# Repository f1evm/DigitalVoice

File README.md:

# DigitalVoice
An open source codec2 based handheld digital radio for VHF/UHF amateur bands

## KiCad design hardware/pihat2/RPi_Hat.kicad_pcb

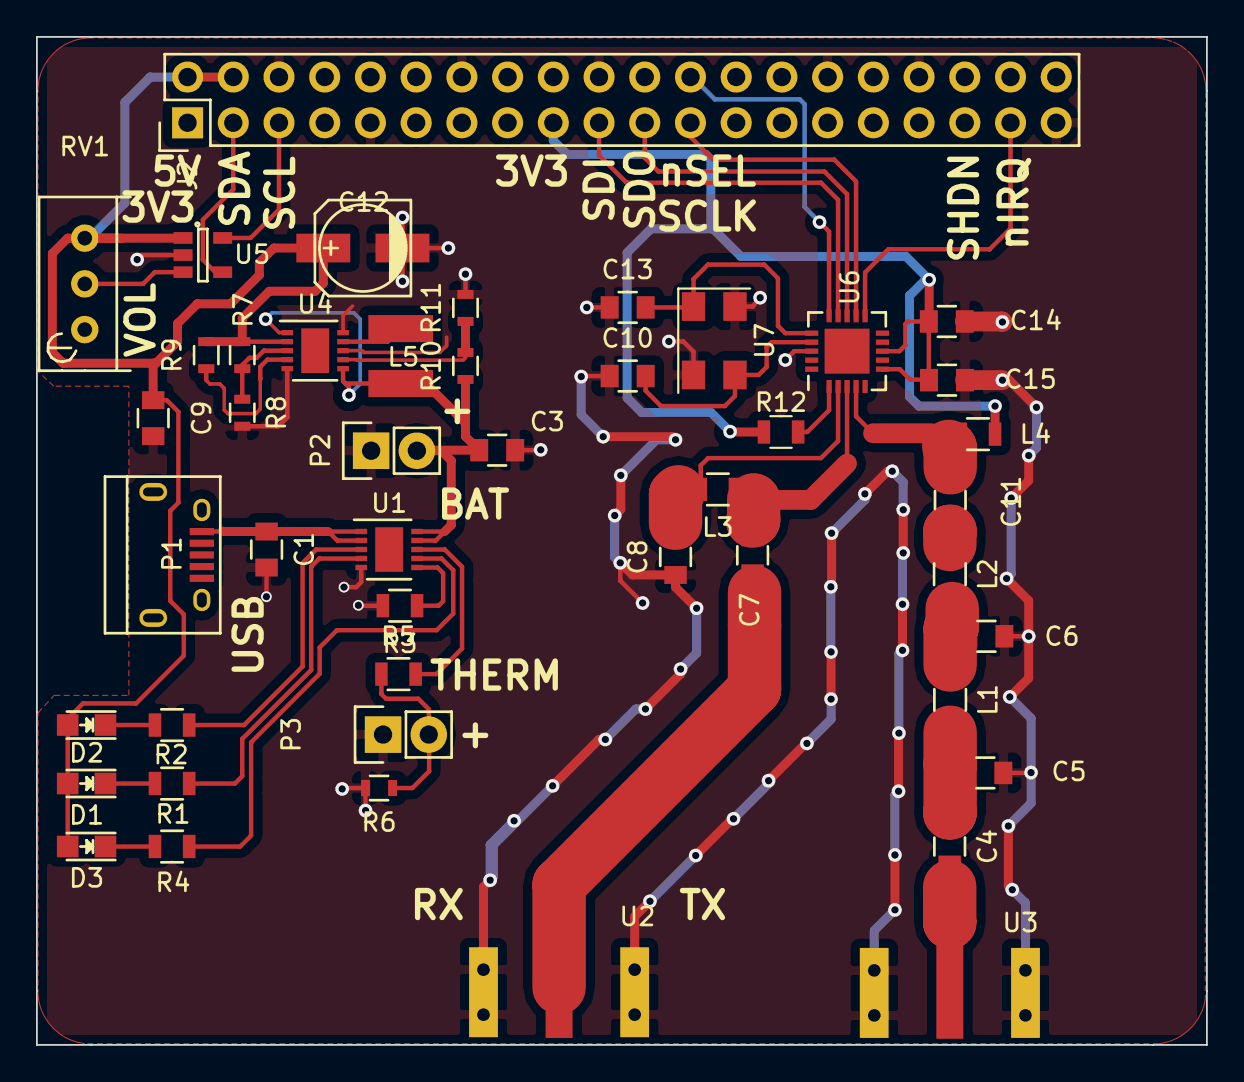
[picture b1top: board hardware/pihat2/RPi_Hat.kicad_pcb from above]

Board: 2 copper layers, 65.0 x 56.0 mm, 46 parts (0 on the bottom side), 34 nets.

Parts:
C1, C3, C9: 10uF; C_0805
C4, C5, C6, C7, C8, C11: C; C_0805
C10, C13: 12pF; C_0805
C12: 47uF; c_elec_5x5.3
C14, C15: 10nF; C_0805
D1, D2, D3: LED; LED_0805
J2: RPi_GPIO; Pin_Header_Straight_2x20
L1, L2, L3, L4: L_Small; R_0805
L5: 6.8uH; BOURNES_SRN4018
P1: USB_OTG; USB_Micro-B
P2: BATT; Pin_Header_Straight_1x02
P3: THERM; Pin_Header_Straight_1x02
R1, R2, R3, R4, R5, R12: 1K; R_0805
R6: 150K; R_0603
R7, R8, R9, R10, R11: R; R_0603
RV1: POT; Potentiometer_Bourns_3296W_3-8Zoll_Inline_ScrewUp
U1: MCP73833; DFN-10-1EP_3x3mm_Pitch0.5mm
U2, U3: SMA_Edge_Mount
U4: TPS61027; DFN-10-1EP_3x3mm_Pitch0.5mm
U5: MCP3021; SOT-23-5
U6: Si4464; QFN-20-1EP_4x4mm_Pitch0.5mm
U7: 30MHz; Crystal_SMD_Abracon_ABM3C-4pin_5.0x3.2mm

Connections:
5VU: C9.1, C12.1, J2.2, J2.4, R7.1, R9.2, RV1.2, U4.2, U5.1
+3V3: C14.2, C15.2, J2.1, J2.17, L4.1, R12.1, U6.6, U6.8
GND: C1.2, C3.2, C5.2, C6.2, C8.1, C9.2, C10.1, C12.2, C13.1, C14.1, C15.1, J2.6, J2.9, J2.14, J2.20, J2.25, J2.30, J2.34, J2.39, P2.1, P3.1, R3.2, R6.2, R8.2, R11.2, U1.5, U2.1, U2.3, U3.1, U3.3, U4.5, U4.8, U4.10, U5.2, U6.18, U7.2, U7.4
unnamed: C4.1, C5.1, L1.2
unnamed: C6.1, L1.1, L2.2
unnamed: C7.1, L3.1, U6.3
unnamed: C8.2, L3.2, U6.2
unnamed: C10.2, U6.17, U7.3
unnamed: C11.1, L4.2, U6.4
unnamed: C11.2, L2.1
unnamed: C13.2, U6.16, U7.1
unnamed: L5.1, U4.9
unnamed: P3.2, R5.1, R6.1
unnamed: R1.2, U1.4
unnamed: R2.2, U1.3
unnamed: R3.1, U1.6
unnamed: R4.2, U1.7
unnamed: R5.2, U1.8
unnamed: R7.2, R8.1, U4.3
unnamed: R9.1, U4.4
unnamed: R10.2, R11.1, U4.7
unnamed: R12.2, U6.1
RXI: C7.2, U2.2
SCL: J2.5, U5.5
SCLK: J2.23, U6.12
SDA: J2.3, U5.4
SDI: J2.19, U6.14
SDO: J2.21, U6.13
TXO: C4.2, U3.2
USB_5V: C1.1, U1.1, U1.2
VBAT: C3.1, L5.2, P2.2, R10.1, U1.9, U1.10, U4.1, U4.6
VOL: RV1.1, U5.3
nIRQ: J2.37, U6.11
nSEL: J2.24, U6.15

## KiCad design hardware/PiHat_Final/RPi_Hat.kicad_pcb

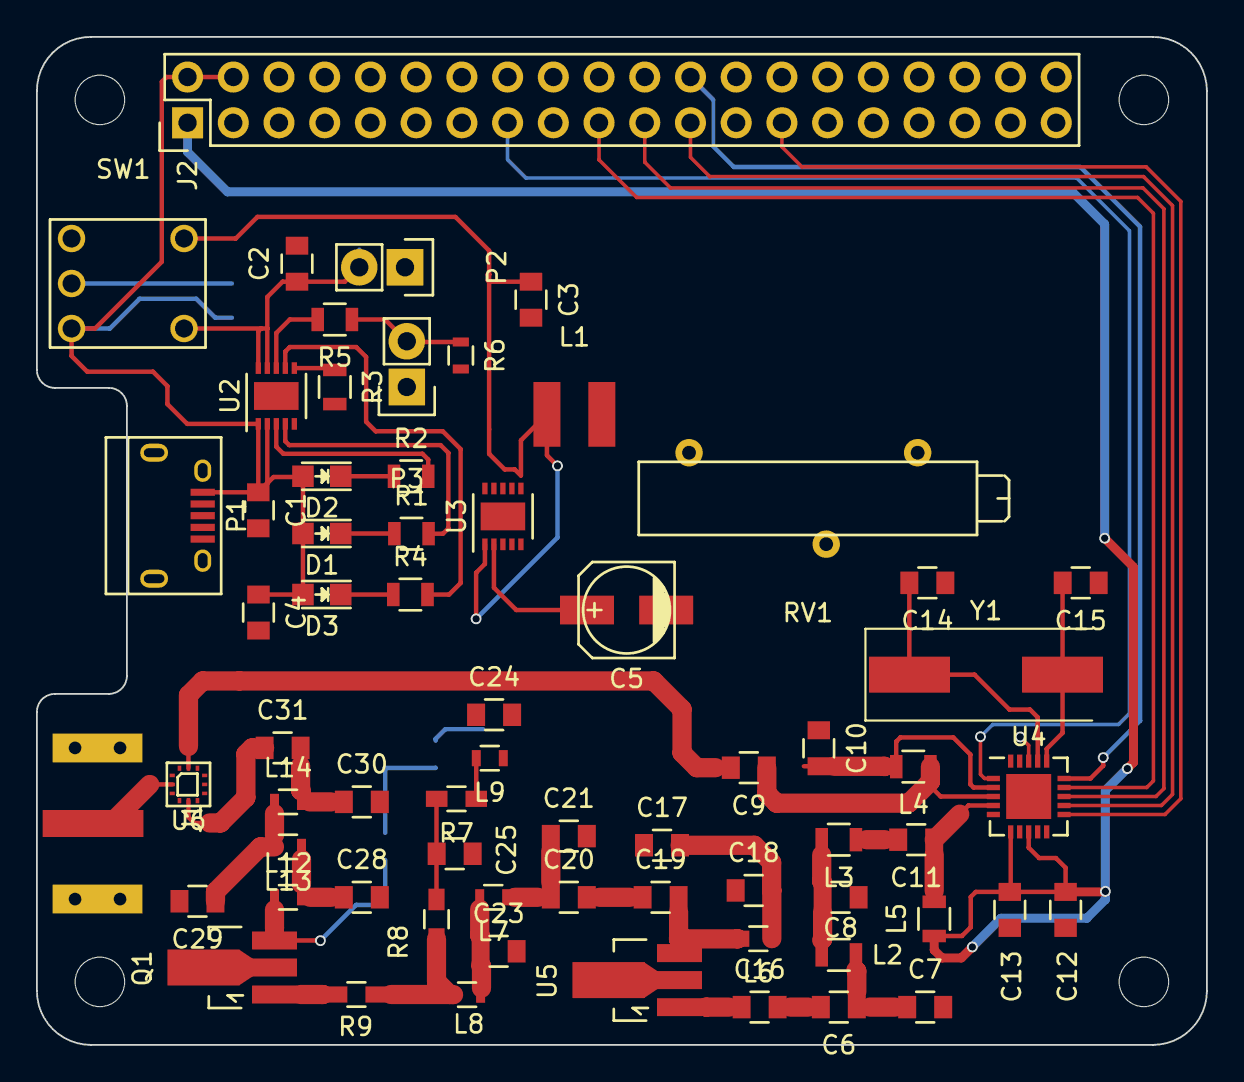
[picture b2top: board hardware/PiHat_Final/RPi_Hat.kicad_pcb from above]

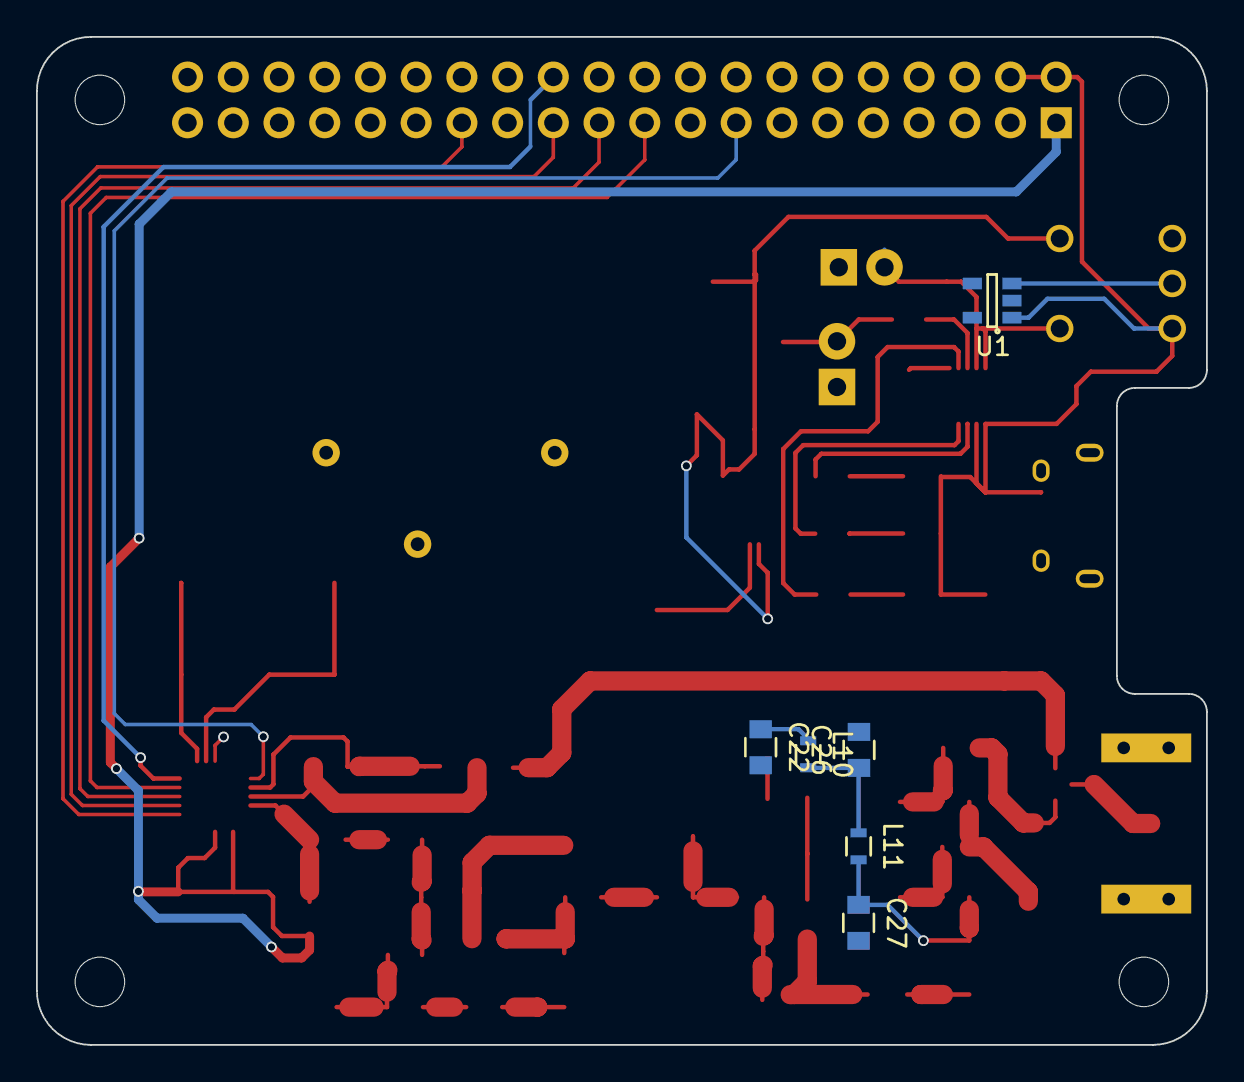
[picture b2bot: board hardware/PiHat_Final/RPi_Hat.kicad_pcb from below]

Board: 2 copper layers, 65.0 x 56.0 mm, 72 parts (6 on the bottom side), 49 nets.

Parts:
C1, C2, C3, C4: 10uF; C_0805
C5: 47uF; c_elec_5x5.3
C6, C9, C11: 4.7pF; C_0805
C7: 5.1pF; C_0805
C8: 12pF; C_0805
C10: 5.6pF; C_0805
C12, C13: 10nF; C_0805
C14, C15: 20pF; C_0805
C16, C17, C18, C19, C20, C21, C22, C23, C24, C25, C26, C27, C28, C29, C30, C31: C; C_0805
D1, D2, D3: LED; LED_0805
J1: SMACONN; SMA_Edge_Mount
J2: RPi_GPIO; Pin_Header_Straight_2x20
L1: 6.8uH; BOURNES_SRN4018
L2: 11nH; R_0805
L3: 27nH; R_0805
L4, L5: 36nH; R_0805
L6, L7, L8, L9, L10, L11, L12, L13, L14: L_Small; R_0603
P1: USB_OTG; USB_Micro-B
P2: BATT; Pin_Header_Straight_1x02
P3: THERM; Pin_Header_Straight_1x02
Q1: AFT05MS003N; SOT89-3_Housing_Handsoldering
R1, R2, R3, R4, R5: 1K; R_0805
R6: 150K; R_0603
R7, R8, R9: R; R_0603_HandSoldering
RV1: POT; Potentiometer_Bourns_3006W_Angular_ScrewFront
SW1: PWR_VOL; rotary_potentiometer
U1: MCP3021; SOT-23-5
U2: MCP73833; DFN-10-1EP_3x3mm_Pitch0.5mm
U3: TPS61027; DFN-10-1EP_3x3mm_Pitch0.5mm
U4: Si4464; QFN-20-1EP_4x4mm_Pitch0.5mm
U5: MMG3H21NT1; SOT89-3_Housing_Handsoldering
U6: SKY13374; QFN_12_2mmx2mm_0.5PITCH
Y1: 30MHz; Crystal_SMD_HC49-SD

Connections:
5VU: C1.1, C4.1, C5.1, C17.2, C18.2, C22.1, D1.2, D2.2, D3.2, J2.2, J2.4, L6.1, L10.1, P1.1, RV1.1, SW1.1, U1.1, U2.1, U2.2, U3.2
+3V3: C12.2, C13.2, J2.1, J2.17, L5.1, U4.6, U4.8, U6.9
GND: C1.2, C2.2, C3.2, C4.2, C5.2, C7.2, C8.2, C10.1, C12.1, C13.1, C14.1, C15.1, C17.1, C18.1, C21.2, C22.2, C23.2, C24.2, C25.2, C26.2, C27.2, C28.2, C29.2, C30.2, J1.2, J2.6, J2.9, J2.14, J2.20, J2.25, J2.30, J2.39, P1.5, P1.6, P2.1, P3.1, Q1.2, R3.2, R6.2, RV1.3, SW1.3, U1.2, U2.5, U3.5, U3.8, U3.10, U4.18, U5.2, U6.3, U6.4, U6.6, U6.10, U6.12
MISO: J2.21, U4.13
MOSI: J2.19, U4.14
unnamed: C6.1, C7.1, L2.2
unnamed: C8.1, L2.1, L3.2
unnamed: C9.1, L4.1, U4.3
unnamed: C10.2, L4.2, U4.2
unnamed: C11.1, L5.2, U4.4
unnamed: C11.2, L3.1
unnamed: C14.2, U4.17, Y1.1
unnamed: C15.2, U4.16, Y1.2
unnamed: C16.1, U5.1
unnamed: C19.1, C20.2
unnamed: C19.2, L6.2, U5.3
unnamed: C20.1, C21.1, L7.1
unnamed: C23.1, L7.2, L8.1
unnamed: C24.1, L9.2, R7.1
unnamed: C25.1, R7.2, R8.1
unnamed: C26.1, L10.2, L11.1
unnamed: C27.1, L11.2, L12.1, Q1.3
unnamed: C28.1, L12.2, L13.1
unnamed: C29.1, L13.2, L14.1
unnamed: C30.1, C31.2, L14.2
unnamed: D1.1, R1.1
unnamed: D2.1, R2.1
unnamed: D3.1, R4.1
unnamed: J1.1, U6.2
unnamed: L1.1, U3.9
unnamed: L8.2, R8.2, R9.2
unnamed: L9.1, RV1.2
unnamed: P3.2, R5.1, R6.1
unnamed: Q1.1, R9.1
unnamed: R1.2, U2.4
unnamed: R2.2, U2.3
unnamed: R3.1, U2.6
unnamed: R4.2, U2.7
unnamed: R5.2, U2.8
RXI: C9.2, U6.11
SCLK: J2.23, U4.12
SHDN: J2.15, U4.1
TXO: C6.2, C16.2
TX_PWR: C31.1, U6.5
VBAT: C3.1, L1.2, SW1.5, U3.1, U3.6
VBP_SW: C2.1, P2.2, SW1.4, U2.9, U2.10
VOL: SW1.2, U1.3
nIRQ: J2.27, U4.11
nSEL: J2.24, U4.15

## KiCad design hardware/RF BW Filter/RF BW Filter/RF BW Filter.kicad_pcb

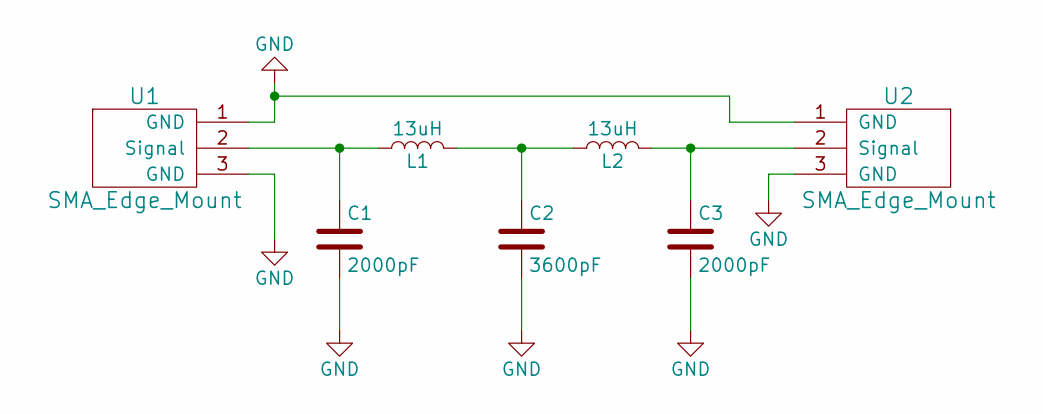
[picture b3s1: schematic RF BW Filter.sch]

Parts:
C1, C3: 2000pF; C_0805
C2: 3600pF; C_0805
L1, L2: 13uH; R_0805
U1, U2: SMA_Edge_Mount

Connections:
GND: C1.2, C2.2, C3.2, U1.1 (GND), U1.3 (GND), U2.1 (GND), U2.3 (GND)
unnamed: C1.1, L1.1, U1.2 (Signal)
unnamed: C2.1, L1.2, L2.1
unnamed: C3.1, L2.2, U2.2 (Signal)

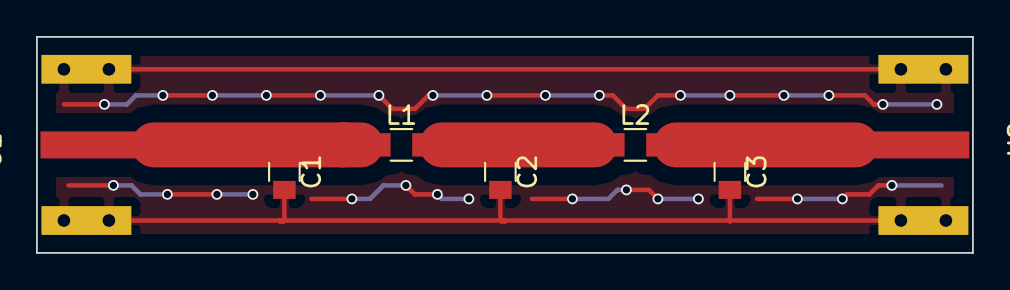
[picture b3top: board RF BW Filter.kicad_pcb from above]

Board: 2 copper layers, 52.0 x 12.0 mm, 7 parts (0 on the bottom side), 4 nets.

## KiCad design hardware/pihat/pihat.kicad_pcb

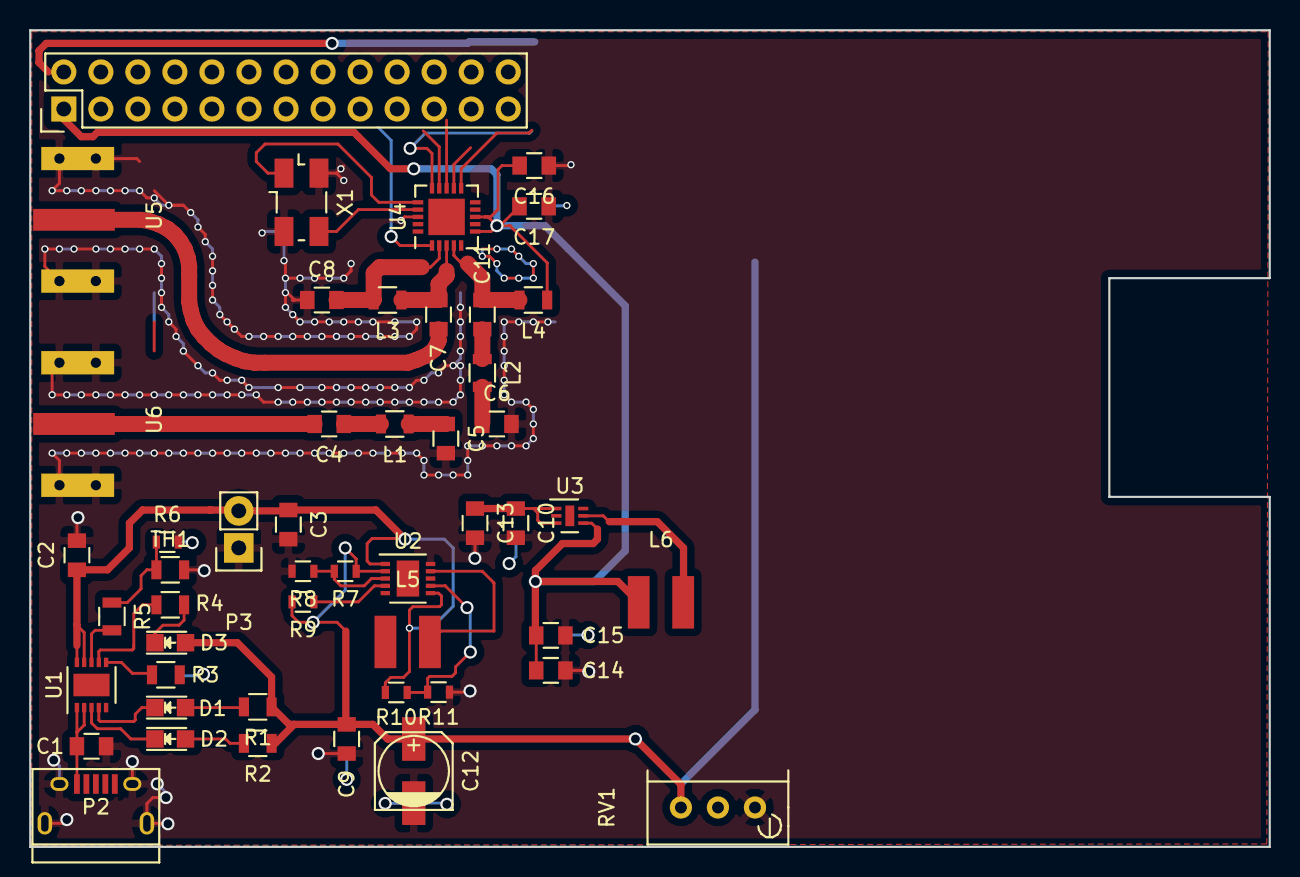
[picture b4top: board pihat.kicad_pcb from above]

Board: 2 copper layers, 85.0 x 56.0 mm, 49 parts (0 on the bottom side), 35 nets.

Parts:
C1, C2, C3, C9, C10, C13, C14, C15: 10uF; C_0805
C4, C5, C6, C7, C8, C11: C; C_0805
C12: 47uF; c_elec_5x5.3
C16, C17: 10nF; C_0805
D1, D2, D3: LED; LED_0805
L1, L2, L3, L4: L_Small; R_0805
L5: 6.8uH; BOURNES_SRN4018
L6: 1uH; BOURNES_SRN4018
P1: CONN_13X2; Pin_Header_Straight_2x13
P2: USB_OTG; USB_Micro-B
P3: BATT; Pin_Header_Straight_1x02
R1, R2, R3, R4, R5: 1K; R_0805
R6: 150K; R_0603
R7, R8, R9, R10, R11: R; R_0603
RV1: POT; Potentiometer_Bourns_3296W_3-8Zoll_Inline_ScrewUp
TH1: 10K; R_0805
U1: MCP73833; DFN-10-1EP_3x3mm_Pitch0.5mm
U2: TPS61027; DFN-10-1EP_3x3mm_Pitch0.5mm
U3: SC189; DFN-6-1EP_2x2mm_Pitch0.5mm
U4: Si4464; QFN-20-1EP_4x4mm_Pitch0.5mm
U5, U6: SMA_Edge_Mount
X1: 30MHz; Crystal_SMD_5032_4Pads

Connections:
5VU: C1.1, C9.1, C10.1, C12.1, C13.1, D3.2, L5.2, P1.2, P2.1, R1.1, R2.1, R7.1, R9.2, RV1.3, U1.1, U1.2, U2.2, U3.1, U3.3
+3V3: C14.1, C15.1, C16.2, C17.2, L4.1, L6.2, P1.1, U3.4, U4.6, U4.8
GND: C1.2, C2.2, C3.2, C5.2, C6.2, C8.1, C9.2, C10.2, C12.2, C13.2, C14.2, C15.2, C16.1, C17.1, P1.6, P2.5, P2.6, P3.1, R3.2, R6.2, R8.2, R11.2, RV1.1, TH1.2, U1.5, U2.5, U2.8, U2.10, U3.2, U4.18, U5.1, U5.3, U6.1, U6.3, X1.3
unnamed: C4.1, C5.1, L1.2
unnamed: C6.1, L1.1, L2.2
unnamed: C7.1, L3.1, U4.3
unnamed: C8.2, L3.2, U4.2
unnamed: C11.1, L4.2, U4.4
unnamed: C11.2, L2.1
unnamed: D1.1, U1.4
unnamed: D1.2, R1.2
unnamed: D2.1, U1.3
unnamed: D2.2, R2.2
unnamed: D3.1, R4.1
unnamed: L5.1, U2.9
unnamed: L6.1, U3.5
unnamed: R3.1, U1.6
unnamed: R4.2, U1.7
unnamed: R5.1, R6.1, TH1.1
unnamed: R5.2, U1.8
unnamed: R7.2, R8.1, U2.3
unnamed: R9.1, U2.4
unnamed: R10.2, R11.1, U2.7
unnamed: U4.16, X1.1
unnamed: U4.17, X1.2
RXI: C7.2, U5.2
SCLK: P1.23, U4.12
SDI: P1.19, U4.14
SDO: P1.21, U4.13
SHDN: P1.18, U4.1
TXO: C4.2, U6.2
VBAT: C2.1, C3.1, P3.2, R10.1, U1.9, U1.10, U2.1, U2.6
VOL: P1.15, RV1.2
nIRQ: P1.22, U4.11
nSEL: P1.24, U4.15

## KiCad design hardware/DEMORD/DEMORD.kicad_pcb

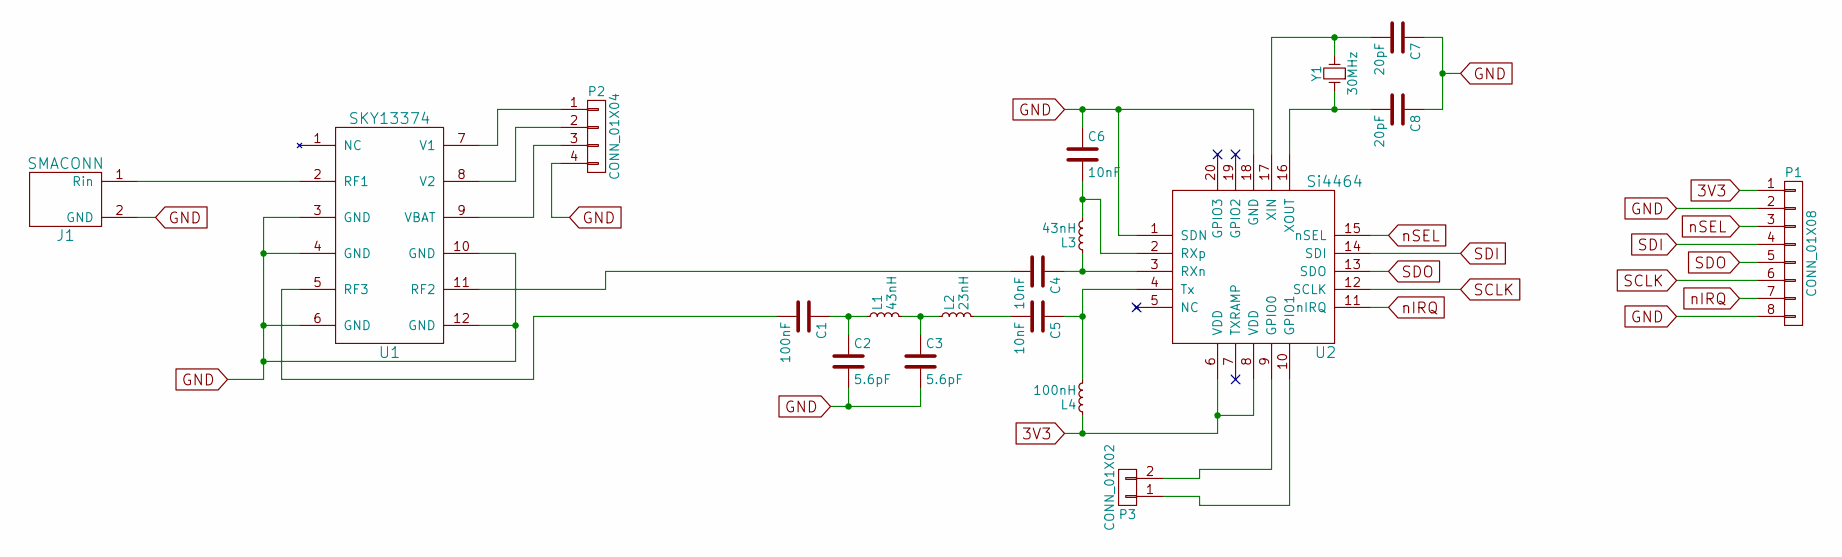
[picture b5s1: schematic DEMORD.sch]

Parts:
C1: 100nF; C_0805
C2, C3: 5.6pF; C_0805
C4, C5, C6: 10nF; C_0805
C7, C8: 20pF; C_0805
J1: SMACONN; SMA_CONN
L1, L3: 43nH; R_0805
L2: 23nH; R_0805
L4: 100nH; R_0805
P1: CONN_01X08; Pin_Header_Straight_1x08_Pitch1.27mm
P2: CONN_01X04; Pin_Header_Straight_1x04_Pitch1.27mm
P3: CONN_01X02; Pin_Header_Straight_1x02_Pitch1.27mm
U1: SKY13374; QFN_12_2mmx2mm_0.5PITCH
U2: Si4464; QFN-20-1EP_4x4mm_Pitch0.5mm
Y1: 30MHz; Crystal_SMD_HC49-SD_HandSoldering

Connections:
3V3: L4.1, P1.1, U2.6 (VDD), U2.8 (VDD)
GND: C2.2, C3.2, C6.1, C7.1, C8.1, J1.2 (GND), P1.2, P1.8, P2.4, U1.3 (GND), U1.4 (GND), U1.6 (GND), U1.10 (GND), U1.12 (GND), U2.1 (SDN), U2.18 (GND)
unnamed: C1.1, C2.1, L1.1
unnamed: C1.2, U1.5 (RF3)
unnamed: C3.1, L1.2, L2.1
unnamed: C4.1, L3.1, U2.3 (RXn)
unnamed: C4.2, U1.11 (RF2)
unnamed: C5.1, L4.2, U2.4 (Tx)
unnamed: C5.2, L2.2
unnamed: C6.2, L3.2, U2.2 (RXp)
unnamed: C7.2, U2.17 (XIN), Y1.2
unnamed: C8.2, U2.16 (XOUT), Y1.1
unnamed: J1.1 (Rin), U1.2 (RF1)
unnamed: P2.1, U1.7 (V1)
unnamed: P2.2, U1.8 (V2)
unnamed: P2.3, U1.9 (VBAT)
unnamed: P3.1, U2.10 (GPIO1)
unnamed: P3.2, U2.9 (GPIO0)
SCLK: P1.6, U2.12 (SCLK)
SDI: P1.4, U2.14 (SDI)
SDO: P1.5, U2.13 (SDO)
nIRQ: P1.7, U2.11 (nIRQ)
nSEL: P1.3, U2.15 (nSEL)

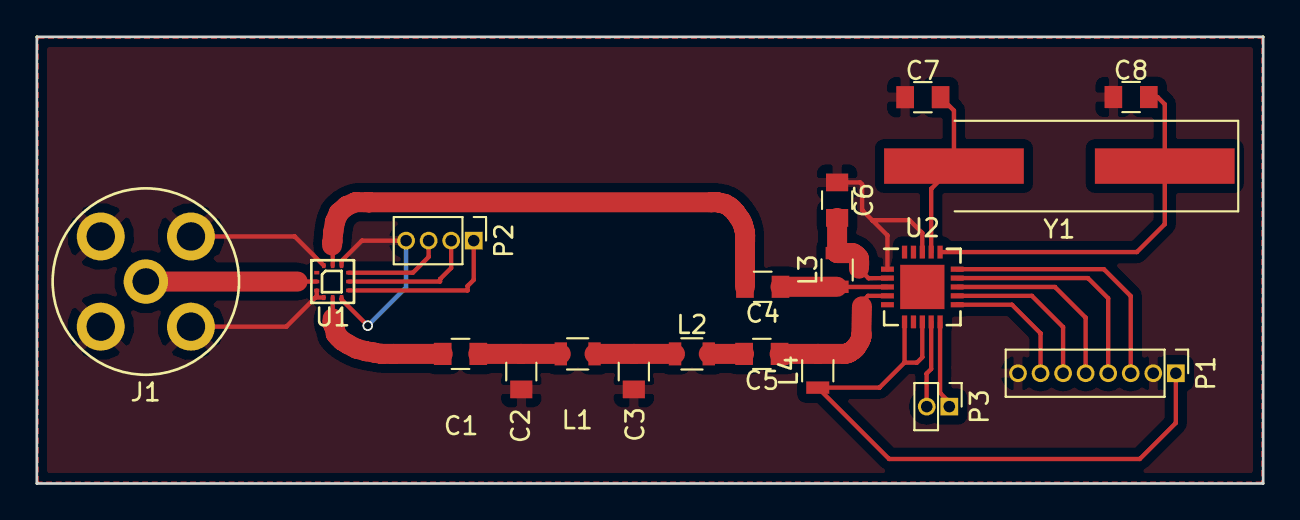
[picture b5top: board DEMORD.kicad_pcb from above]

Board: 2 copper layers, 69.1 x 25.2 mm, 19 parts (0 on the bottom side), 23 nets.

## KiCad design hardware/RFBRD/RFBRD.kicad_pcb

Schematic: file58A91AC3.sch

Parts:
C1, C3, C6: C; C_0805
C2, C5: 5.1pF; C_0805
C4: 4.7pF; C_0805
C7, C8: 10nF; C_0805
C9: 100nF; C_0805
C34: 0.1uF; C_0805
C35: 1uF; C_0805
C36: 10uF; C_0805
C37, C38: 20pF; C_0805
D1, D2: LED; LED_0603
L1: INDUCTOR; Choke_SMD_7.3x7.3_H4.5
L2: 27nH; R_0805
L3, L6: INDUCTOR; R_0805
L4, L5: 100nH; R_0805
P1: CONN_01X08; Pin_Header_Straight_1x08
R13: 1K; R_0805
U1: AX5043; QFN-28-1EP_5x5mm_Pitch0.5mm
W1, W2, W3, W4, W5, W6, W7: TEST_1P; Test_Point_Keystone_5019_Minature
Y1: 16MHz; Crystal_HC49-SD_SMD

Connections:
3V3: C9.1, C34.1, C35.1, C36.1, D2.2 (A), P1.1, U1.23; also elsewhere on the board
GND: C1.2, C3.2, C4.2, C9.2, C34.2, C35.2, C36.2, C37.1, C38.1, D1.1 (K), D2.1 (K), L4.2, L5.1, L6.2, P1.2; also elsewhere on the board
unnamed: C2.1, C5.2, L2.2
unnamed: C3.1, L1.1, L3.2
unnamed: C4.1, L2.1, L4.1, U1.4
unnamed: C5.1, L5.2, U1.3
unnamed: C6.1, L6.1, U1.5
unnamed: C6.2, L3.1
unnamed: C7.1, U1.1
unnamed: C7.2, U1.2
unnamed: C8.1, U1.6
unnamed: C8.2, U1.7
unnamed: C37.2, U1.28, Y1.1
unnamed: C38.2, U1.27, Y1.2
unnamed: D1.2 (A), R13.1
unnamed: R13.2, U1.26
unnamed: U1.9, U1.10
PWRAMP_SEL: U1.20, W1.1; also elsewhere on the board
RF_PREAMP: C1.1, L1.2; also elsewhere on the board
RX_IN: C2.2; also elsewhere on the board
uc_IRQ: P1.3, U1.19, W2.1
uc_MISO: P1.5, U1.16, W4.1
uc_MOSI: P1.4, U1.17, W3.1
uc_clk: P1.6, U1.15, W7.1
uc_sel: P1.7, U1.14, W5.1
uc_sysclk: P1.8, U1.13, W6.1

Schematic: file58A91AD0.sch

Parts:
C10, C17, C22: 100pF; C_0805
C11: 9pF; C_0805
C12: 10nF; C_0805
C13: 10pF; C_0805
C14, C18: 1uF; C_0805
C15, C19: 39pF; C_0805
C16: 10uF; C_0805
C20: 15pF; C_0805
C21: 3.9pF; C_0805
C23, C24: 3.183nF; C_0805
J1: SMACONN; SMA_CONN
L7, L9: 10uH; R_0805
L8: 2.2nH; R_0805
L10, L14: 6.8nH; R_0805
L11: 19nH; R_0805
L12: 1.8nH; R_0805
L13: 5.6nH; R_0805
L15: 16uH; Choke_SMD_12x12mm_h4.5mm
R1: 1.5; R_0603
R2, R3: 22; R_0603
RV1: 47K; Neosid_Air-Coil_SML_2turn_HDM0231A
U2: AFT05M3S003N; SOT-89

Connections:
AMP_PWR_HV: C16.1, C17.1, C18.1, L11.2, RV1.1
GND: C11.2, C12.2, C13.2, C14.2, C15.2, C16.2, C17.2, C18.2, C19.2, C20.2, C21.2, C23.2, C24.2, J1.2, RV1.3, U2.2; also elsewhere on the board
unnamed: C10.1, C11.1, L8.2
unnamed: C12.1, L7.1, L9.2
unnamed: C13.1, L8.1, L10.2
unnamed: C14.1, L9.1, R1.2
unnamed: C19.1, L12.1, L13.2
unnamed: C20.1, L13.1, L14.2
unnamed: C21.1, C22.2, L14.1
unnamed: L7.2, RV1.2
unnamed: L11.1, L12.2, U2.3
unnamed: R1.1, R2.2
unnamed: R3.1, U2.1
PREAMP_TX: C10.2, J1.1; also elsewhere on the board
TX_OUT: C22.1, C23.1, L15.1
TX_PASS: C24.1, L15.2; also elsewhere on the board
VBIAS_PWR: C15.1, L10.1, R2.1, R3.2

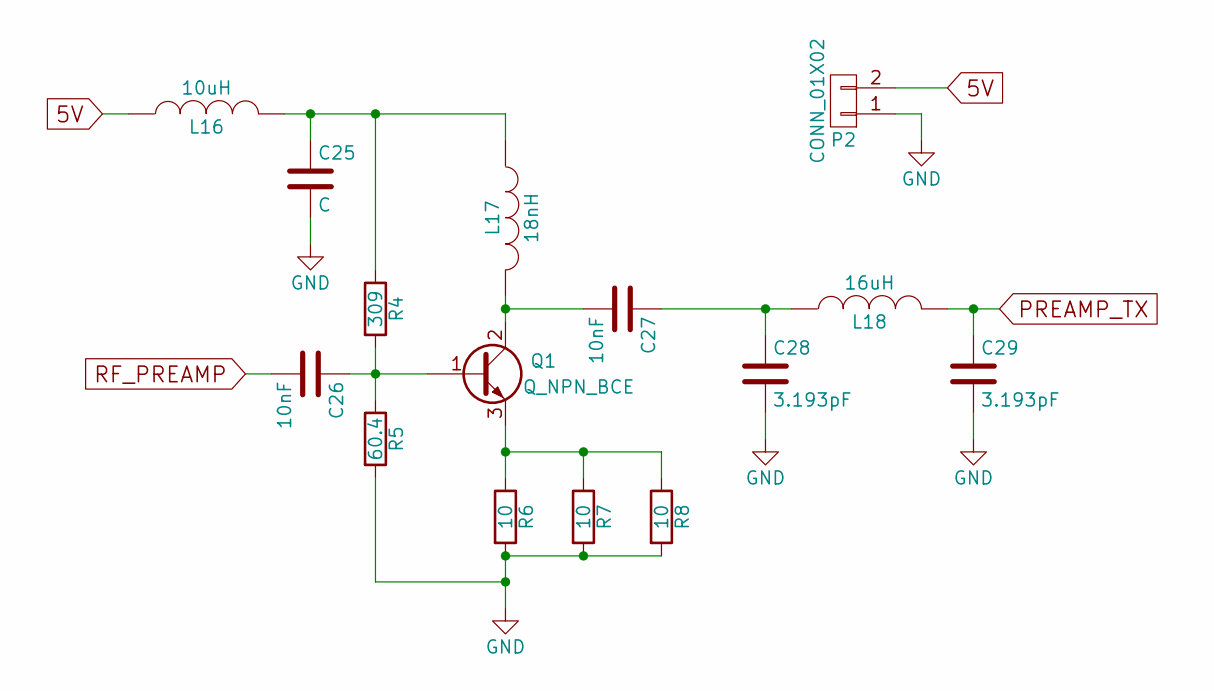
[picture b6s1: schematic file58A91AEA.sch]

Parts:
C25: C; C_0805
C26, C27: 10nF; C_0805
C28, C29: 3.193pF; C_0805
L16: 10uH; R_0805
L17: 18nH; R_0805
L18: 16uH; Choke_SMD_12x12mm_h4.5mm
P2: CONN_01X02; Pin_Header_Straight_1x02
Q1: Q_NPN_BCE; SOT-23
R4: 309; R_0603
R5: 60.4; R_0603
R6, R7, R8: 10; R_0603

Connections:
5V: L16.1, P2.2
GND: C25.2, C28.2, C29.2, P2.1, R5.2, R6.2, R7.2, R8.2; also elsewhere on the board
unnamed: C25.1, L16.2, L17.1, R4.1
unnamed: C26.1, Q1.1 (B), R4.2, R5.1
unnamed: C27.1, C28.1, L18.1
unnamed: C27.2, L17.2, Q1.2 (C)
unnamed: Q1.3 (E), R6.1, R7.1, R8.1
PREAMP_TX: C29.1, L18.2; also elsewhere on the board
RF_PREAMP: C26.2; also elsewhere on the board

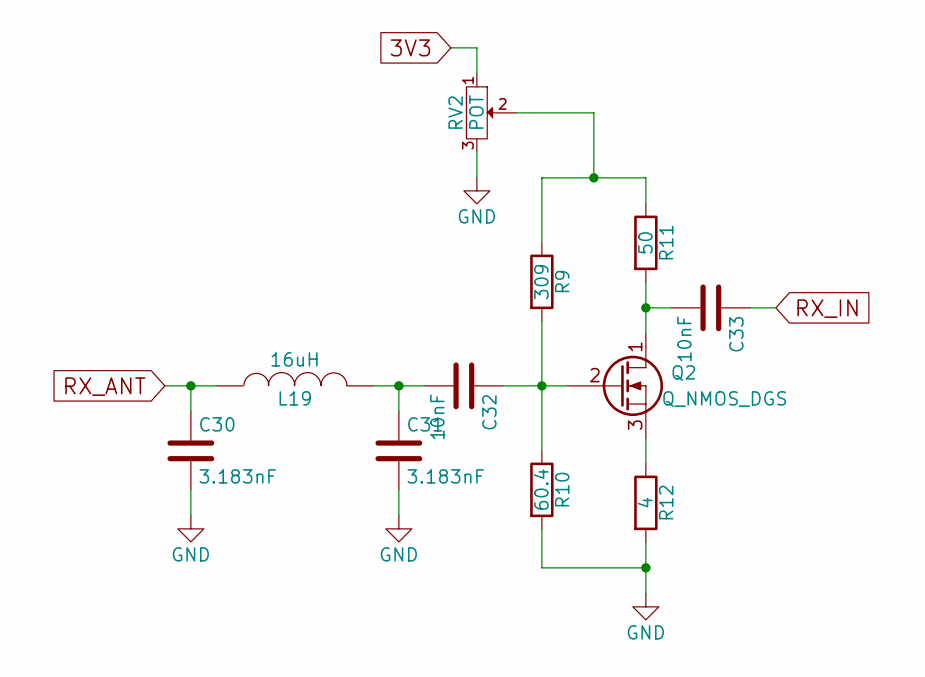
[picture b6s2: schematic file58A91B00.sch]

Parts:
C30, C31: 3.183nF; C_0805
C32, C33: 10nF; C_0805
L19: 16uH; Choke_SMD_12x12mm_h4.5mm
Q2: Q_NMOS_DGS; SOT-23
R9: 309; R_0603
R10: 60.4; R_0603
R11: 50; R_0603
R12: 4; R_0603
RV2: POT; J-FOOT_POT

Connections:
3V3: RV2.1; also elsewhere on the board
GND: C30.2, C31.2, R10.2, R12.2, RV2.3; also elsewhere on the board
unnamed: C31.1, C32.2, L19.2
unnamed: C32.1, Q2.2 (G), R9.2, R10.1
unnamed: C33.2, Q2.1 (D), R11.2
unnamed: Q2.3 (S), R12.1
unnamed: R9.1, R11.1, RV2.2
RX_ANT: C30.1, L19.1; also elsewhere on the board
RX_IN: C33.1; also elsewhere on the board

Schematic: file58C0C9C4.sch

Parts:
J2: SMACONN; SMA_CONN
Q3, Q6: Q_NMOS_DGS; SOT-23
Q4, Q5: Q_PMOS_DGS; SOT-23
U3: SKY13374; QFN_12_2mmx2mm_0.5PITCH

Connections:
3V3: Q3.1 (D), Q5.1 (D); also elsewhere on the board
GND: J2.2, Q4.3 (S), Q6.3 (S), U3.3, U3.4, U3.6, U3.10, U3.12; also elsewhere on the board
unnamed: J2.1, U3.2
PWRAMP_SEL: Q3.2 (G), Q4.2 (G), Q5.2 (G), Q6.2 (G); also elsewhere on the board
RX_ANT: U3.5; also elsewhere on the board
RX_SWITCH: Q5.3 (S), Q6.1 (D), U3.8
TX_PASS: U3.11; also elsewhere on the board
TX_SWITCH: Q3.3 (S), Q4.1 (D), U3.7

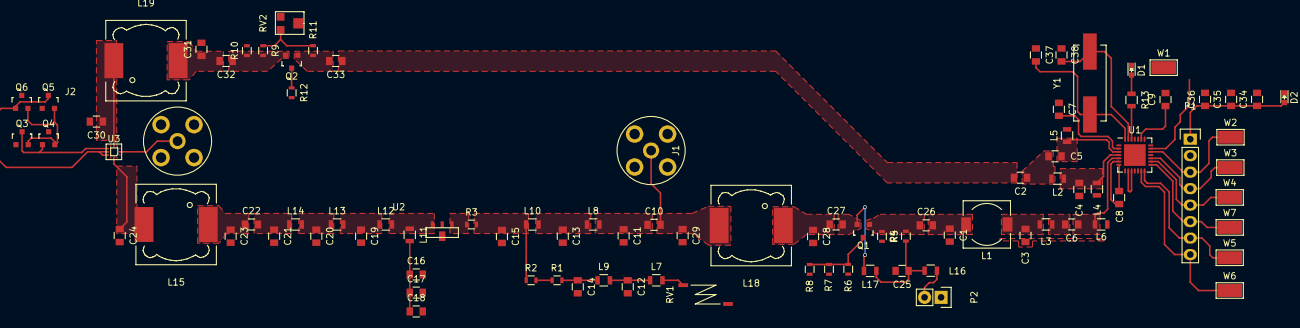
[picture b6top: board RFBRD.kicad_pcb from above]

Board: 4 copper layers, 95 parts (0 on the bottom side), 57 nets.

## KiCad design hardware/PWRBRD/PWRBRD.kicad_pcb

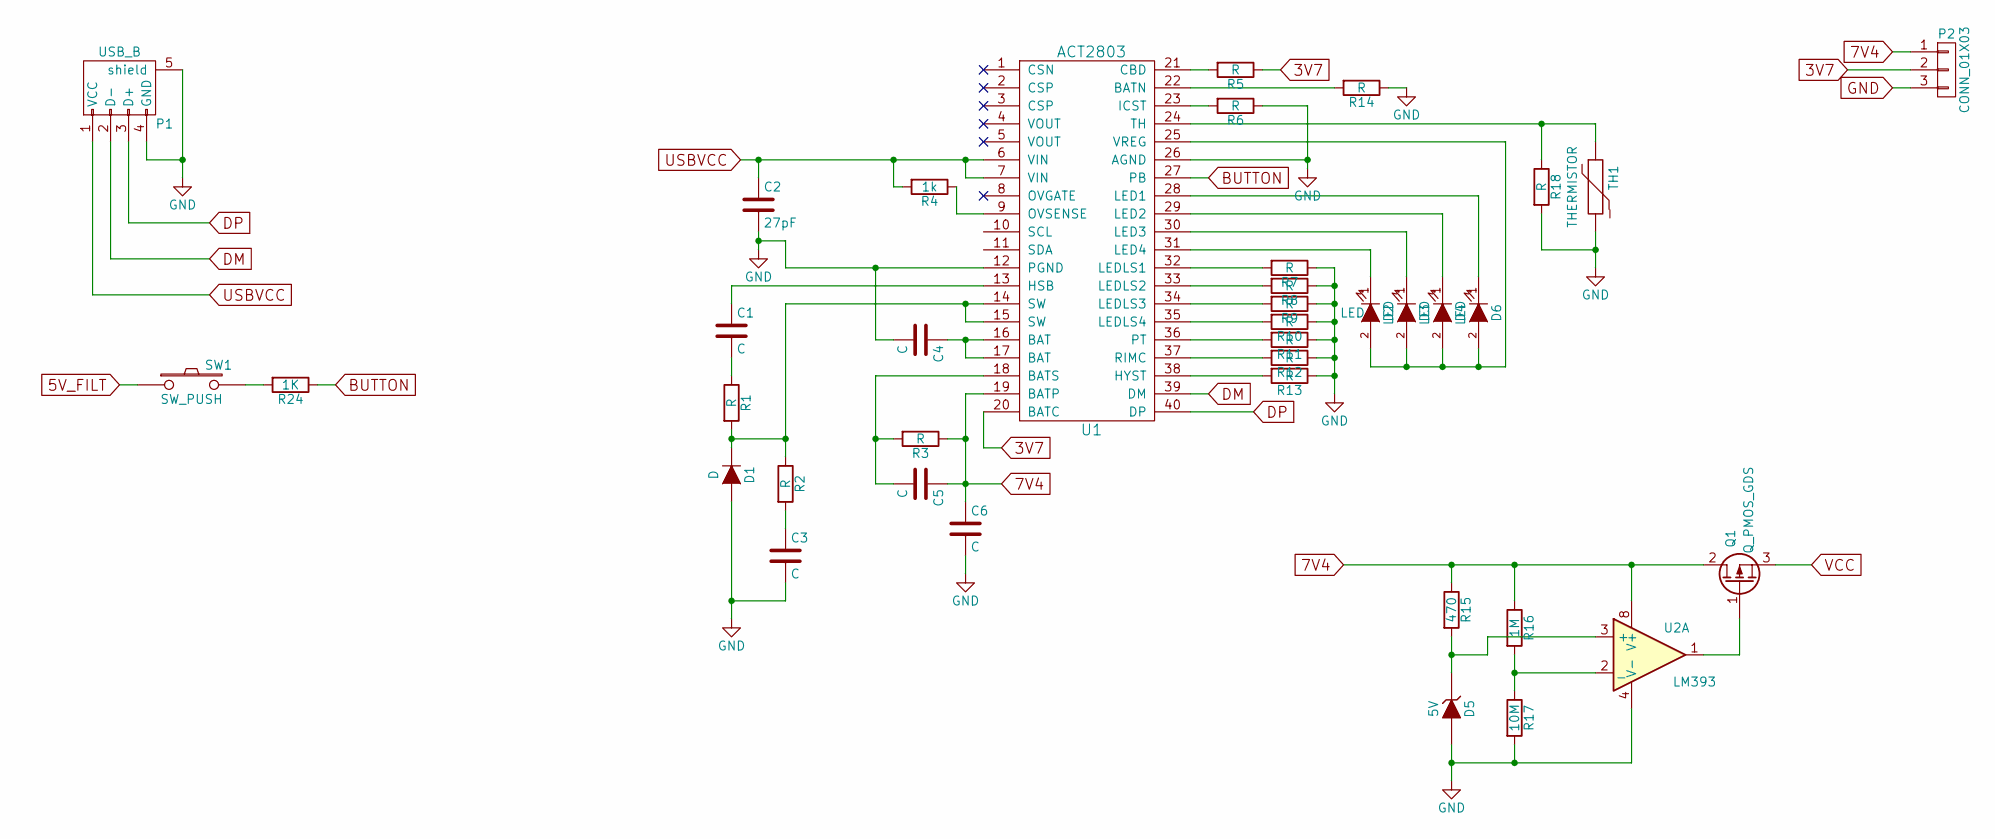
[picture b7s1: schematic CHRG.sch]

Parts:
C1, C3, C4, C5, C6: C; C_0603
C2: 27pF; C_0603
D1: D; R_0603
D2, D3, D4: LED; LED_0603
D5: 5V; R_0603
D6: LED; R_0805
P1: USB_B; USB_Micro-B
P2: CONN_01X03; Pin_Header_Straight_1x03_Pitch1.27mm
Q1: Q_PMOS_GDS; SOT-23
R1, R2, R3, R5, R6, R7, R8, R9, R10, R11, R12, R13, R14, R18: R; R_0603
R4: 1k; R_0603
R15: 470; R_0603
R16: 1M; R_0603
R17: 10M; R_0603
R24: 1K; R_0603
SW1: SW_PUSH; SW_PUSH_6mm
TH1: THERMISTOR; R1
U1: ACT2803; QFN-40-1EP_5x5mm_Pitch0.4mm
U2: LM393; SOIC-8-N

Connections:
3V7: P2.2, R5.1, U1.20 (BATC)
5V: SW1.1; also elsewhere on the board
7V4: C5.1, C6.1, P2.1, Q1.2 (D), R3.1, R15.1, R16.1, U1.19 (BATP), U2.8 (V+)
BUTTON: R24.1, U1.27 (PB)
DM: P1.2 (D-), U1.39 (DM)
DP: P1.3 (D+), U1.40 (DP)
GND: C2.2, C3.2, C4.2, C6.2, D1.2 (A), D5.2 (A), P1.4 (GND), P1.5 (shield), P2.3, R6.1, R7.1, R8.1, R9.1, R10.1, R11.1, R12.1, R13.1, R14.1, R17.2, R18.2, TH1.2, U1.12 (PGND), U1.26 (AGND), U2.4 (V-); also elsewhere on the board
unnamed: C1.1, U1.13 (HSB)
unnamed: C1.2, R1.1
unnamed: C3.1, R2.2
unnamed: C4.1, U1.16 (BAT), U1.17 (BAT)
unnamed: C5.2, R3.2, U1.18 (BATS)
unnamed: D1.1 (K), R1.2, R2.1, U1.14 (SW), U1.15 (SW)
unnamed: D2.1 (K), U1.31 (LED4)
unnamed: D2.2 (A), D3.2 (A), D4.2 (A), D6.2 (A), U1.25 (VREG)
unnamed: D3.1 (K), U1.30 (LED3)
unnamed: D4.1 (K), U1.29 (LED2)
unnamed: D5.1 (K), R15.2, U2.3 (+)
unnamed: D6.1 (K), U1.28 (LED1)
unnamed: Q1.1 (G), U2.1
unnamed: R4.1, U1.9 (OVSENSE)
unnamed: R5.2, U1.21 (CBD)
unnamed: R6.2, U1.23 (ICST)
unnamed: R7.2, U1.32 (LEDLS1)
unnamed: R8.2, U1.33 (LEDLS2)
unnamed: R9.2, U1.34 (LEDLS3)
unnamed: R10.2, U1.35 (LEDLS4)
unnamed: R11.2, U1.36 (PT)
unnamed: R12.2, U1.37 (RIMC)
unnamed: R13.2, U1.38 (HYST)
unnamed: R14.2, U1.22 (BATN)
unnamed: R16.2, R17.1, U2.2 (_)
unnamed: R18.1, TH1.1, U1.24 (TH)
unnamed: R24.2, SW1.2
USBVCC: C2.1, P1.1 (VCC), R4.2, U1.6 (VIN), U1.7 (VIN)
VCC: Q1.3 (S); also elsewhere on the board

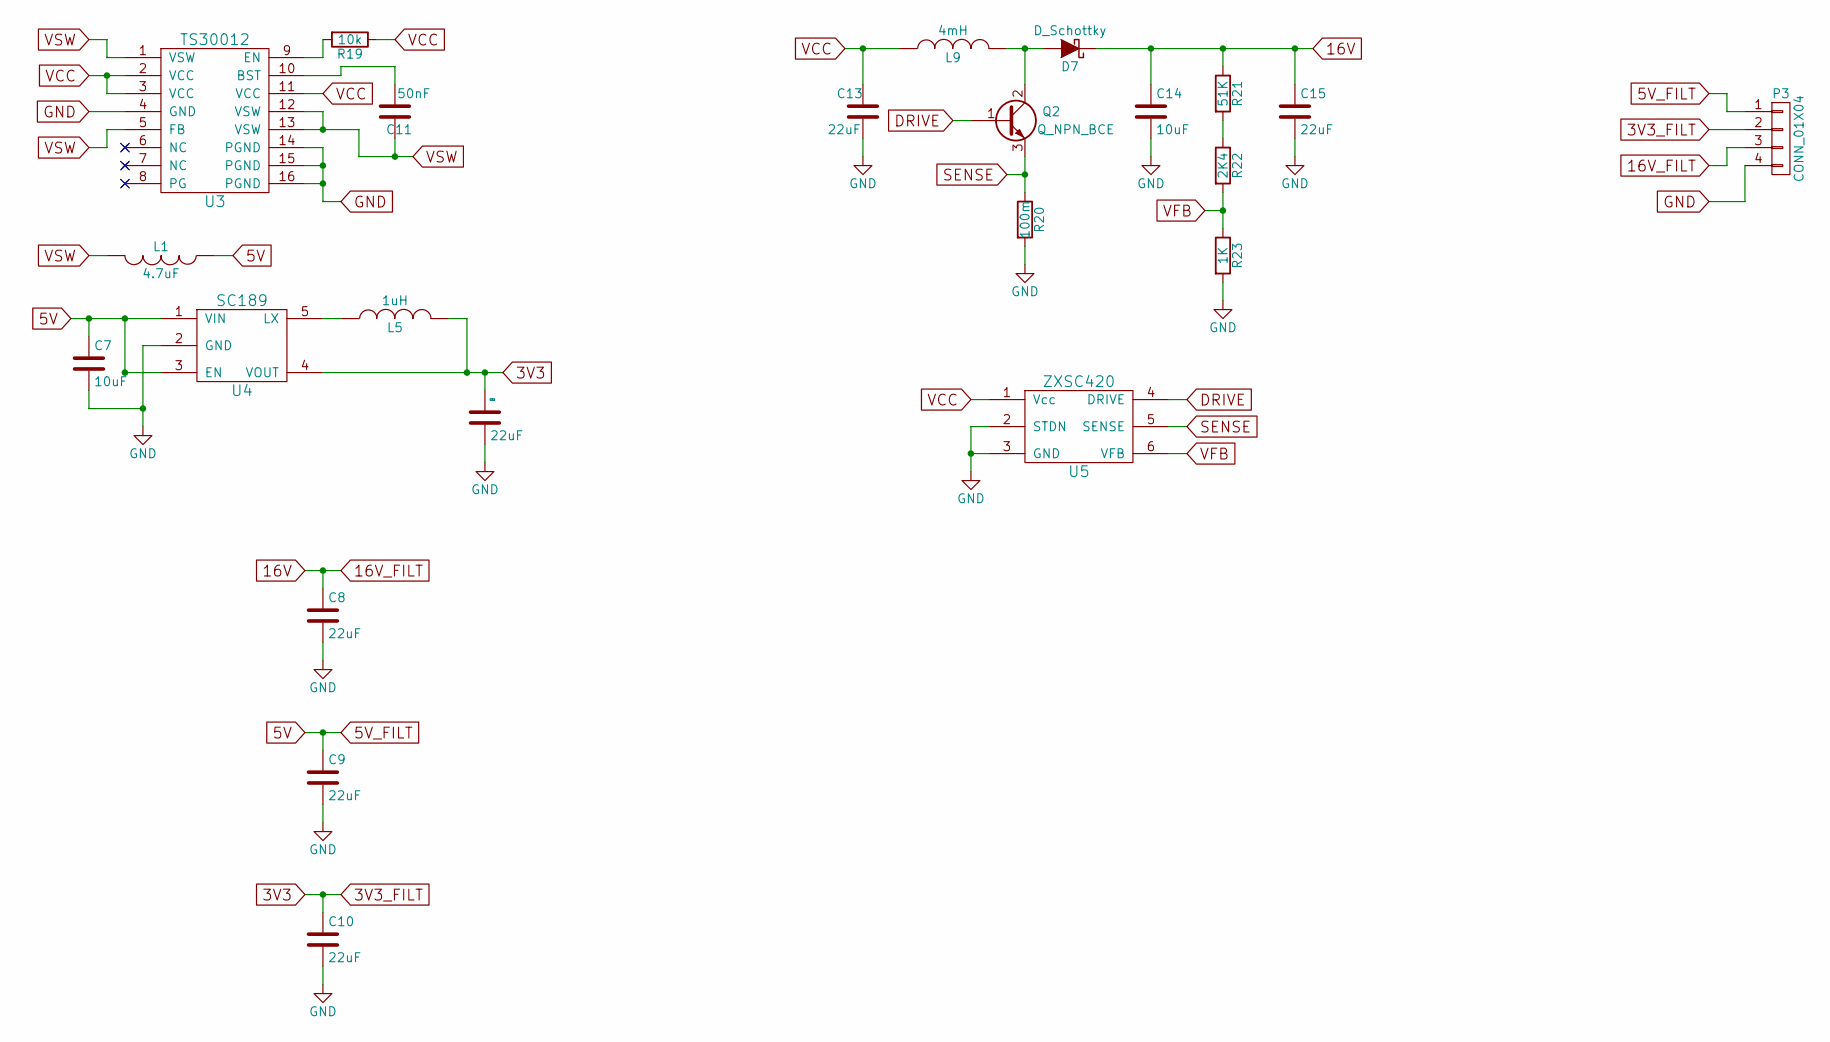
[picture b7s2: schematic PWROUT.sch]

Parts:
C7, C14: 10uF; C_0603
C8, C9, C10, C12, C13, C15: 22uF; CP_Elec_5x5.3
C11: 50nF; C_0603
D7: D_Schottky; R_0603
L1: 4.7uF; R_0805
L5: 1uH; R_0805
L9: 4mH; Choke_Horizontal_RM10mm
P3: CONN_01X04; Pin_Header_Straight_1x04
Q2: Q_NPN_BCE; SOT-23
R19: 10k; R_0603
R20: 100m; R_0603
R21: 51K; R_0603
R22: 2K4; R_0603
R23: 1K; R_0603
U3: TS30012; QFN-16-1EP_3x3mm_Pitch0.5mm
U4: SC189; SOT-23-5
U5: ZXSC420; SOT-23-6

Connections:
3V3: C10.1, C12.1, L5.2, P3.2, U4.4 (VOUT)
5V: C7.1, C9.1, L1.1, P3.1, U4.1 (VIN), U4.3 (EN); also elsewhere on the board
16V: C8.1, C14.1, C15.1, D7.1 (K), P3.3, R21.1
DRIVE: Q2.1 (B), U5.4 (DRIVE)
GND: C7.2, C8.2, C9.2, C10.2, C12.2, C13.2, C14.2, C15.2, P3.4, R20.2, R23.2, U3.4 (GND), U3.14 (PGND), U3.15 (PGND), U3.16 (PGND), U4.2 (GND), U5.2 (STDN), U5.3 (GND); also elsewhere on the board
unnamed: C11.2, U3.10 (BST)
unnamed: D7.2 (A), L9.2, Q2.2 (C)
unnamed: L5.1, U4.5 (LX)
unnamed: R19.2, U3.9 (EN)
unnamed: R21.2, R22.1
SENSE: Q2.3 (E), R20.1, U5.5 (SENSE)
VCC: C13.1, L9.1, R19.1, U3.2 (VCC), U3.3 (VCC), U3.11 (VCC), U5.1 (Vcc); also elsewhere on the board
VFB: R22.2, R23.1, U5.6 (VFB)
VSW: C11.1, L1.2, U3.1 (VSW), U3.5 (FB), U3.12 (VSW), U3.13 (VSW)
